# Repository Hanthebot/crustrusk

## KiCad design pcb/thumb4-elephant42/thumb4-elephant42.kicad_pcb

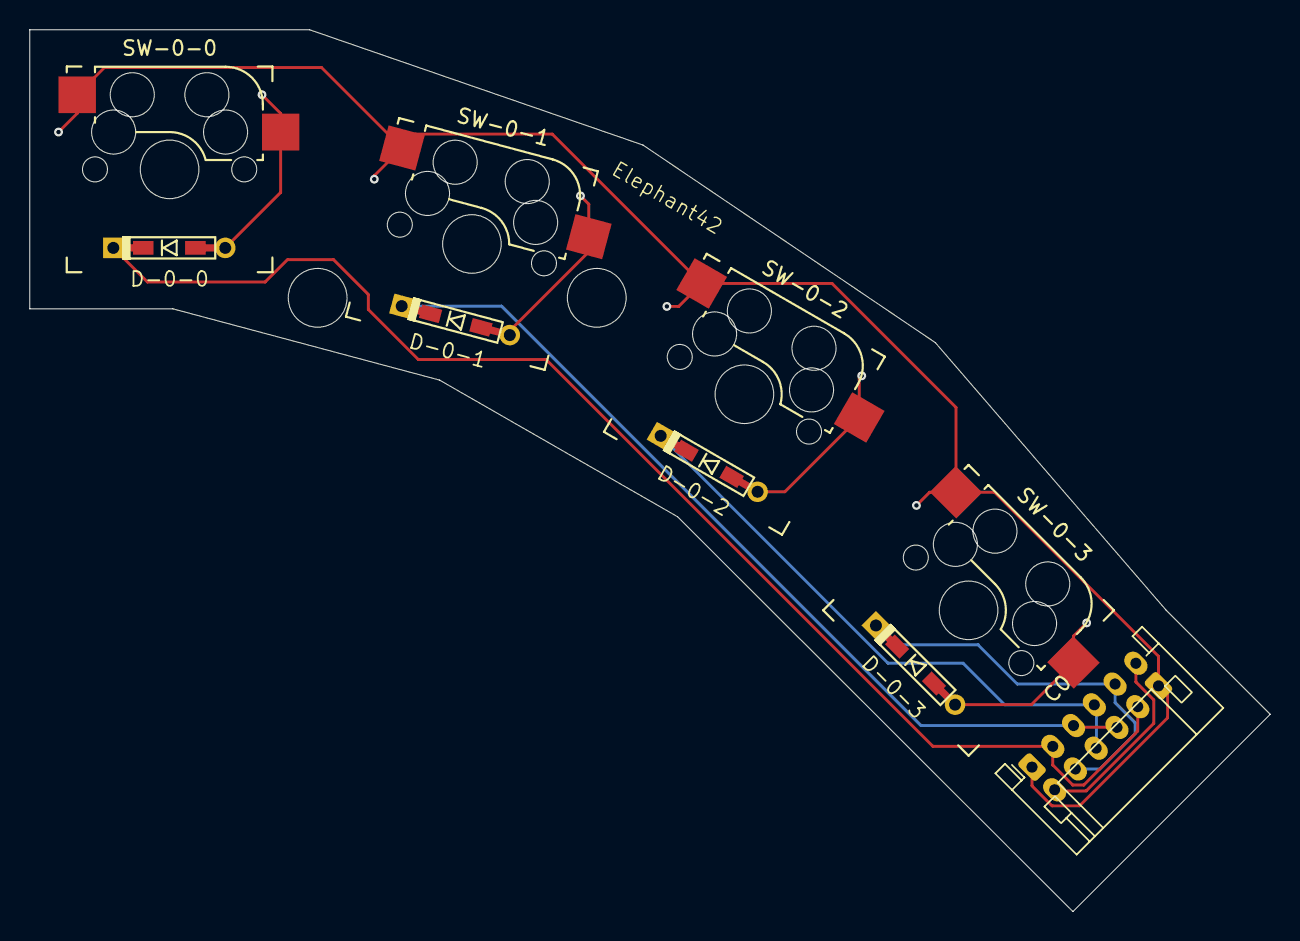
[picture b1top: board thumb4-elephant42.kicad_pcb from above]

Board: 2 copper layers, 84.5 x 60.0 mm, 9 parts (0 on the bottom side), 9 nets.

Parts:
C0: Conn_01x06_Socket; reversible JST_PH_S6B-PH-K_1x06_P2.00mm_Horizontal
D-0-0, D-0-1, D-0-2, D-0-3: D; Diode_TH_SMD_REVERSIBLE
SW-0-0, SW-0-1, SW-0-2, SW-0-3: SW_Push; Kailh_hotswap_only_socket_MX_optional_reversible-MIRROR

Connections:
COL0: C0.1, SW-0-0.2, SW-0-1.2, SW-0-2.2, SW-0-3.2
unnamed: D-0-0.2 (A), SW-0-0.1
unnamed: D-0-1.2 (A), SW-0-1.1
unnamed: D-0-2.2 (A), SW-0-2.1
unnamed: D-0-3.2 (A), SW-0-3.1
ROW0-0: C0.2, D-0-0.1 (K)
ROW1-0: C0.3, D-0-1.1 (K)
ROW2-0: C0.4, D-0-2.1 (K)
ROW3-0: C0.5, D-0-3.1 (K)
